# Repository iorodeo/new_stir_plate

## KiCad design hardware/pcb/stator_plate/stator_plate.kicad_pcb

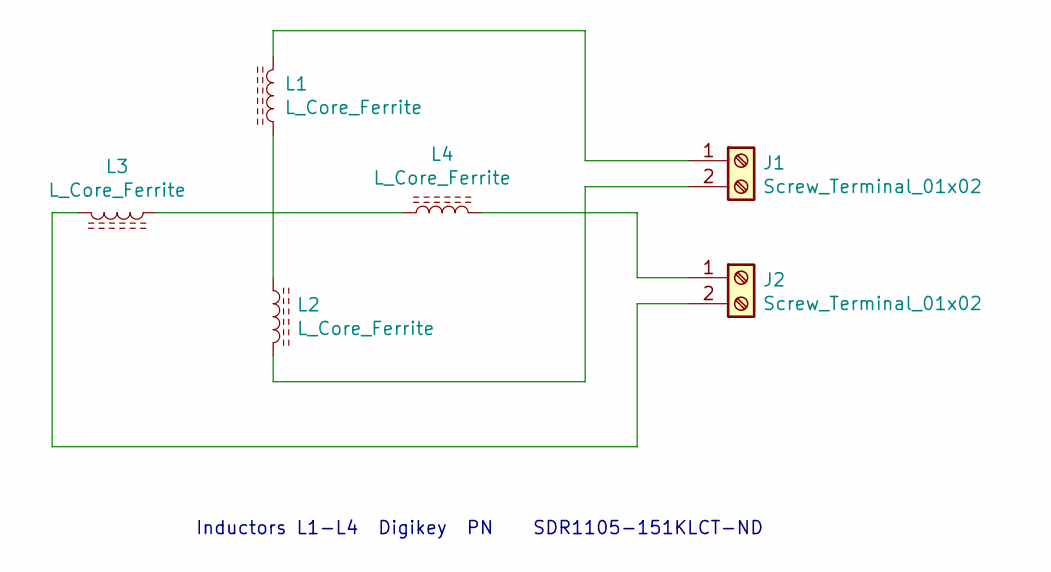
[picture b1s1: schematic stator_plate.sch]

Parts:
J1, J2: Screw_Terminal_01x02; CONNBLOCK2
L1, L2, L3, L4: L_Core_Ferrite; SDR1105

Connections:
unnamed: J1.1, L1.2
unnamed: J1.2, L2.2
unnamed: J2.1, L4.2
unnamed: J2.2, L3.2
unnamed: L1.1, L2.1
unnamed: L3.1, L4.1

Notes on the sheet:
Inductors L1-L4 Digikey PN SDR1105-151KLCT-ND

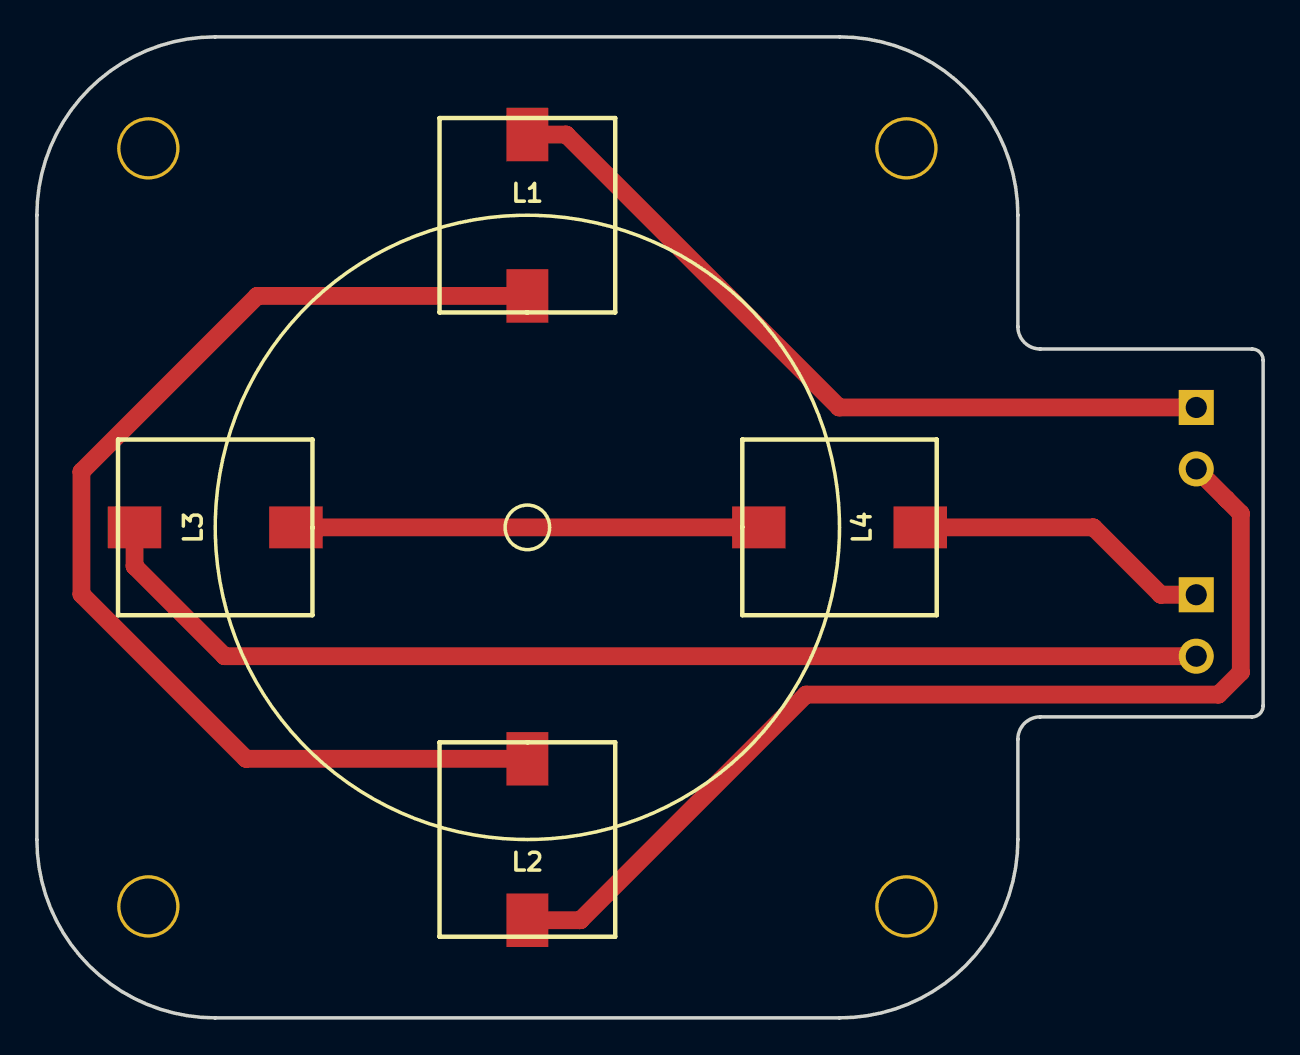
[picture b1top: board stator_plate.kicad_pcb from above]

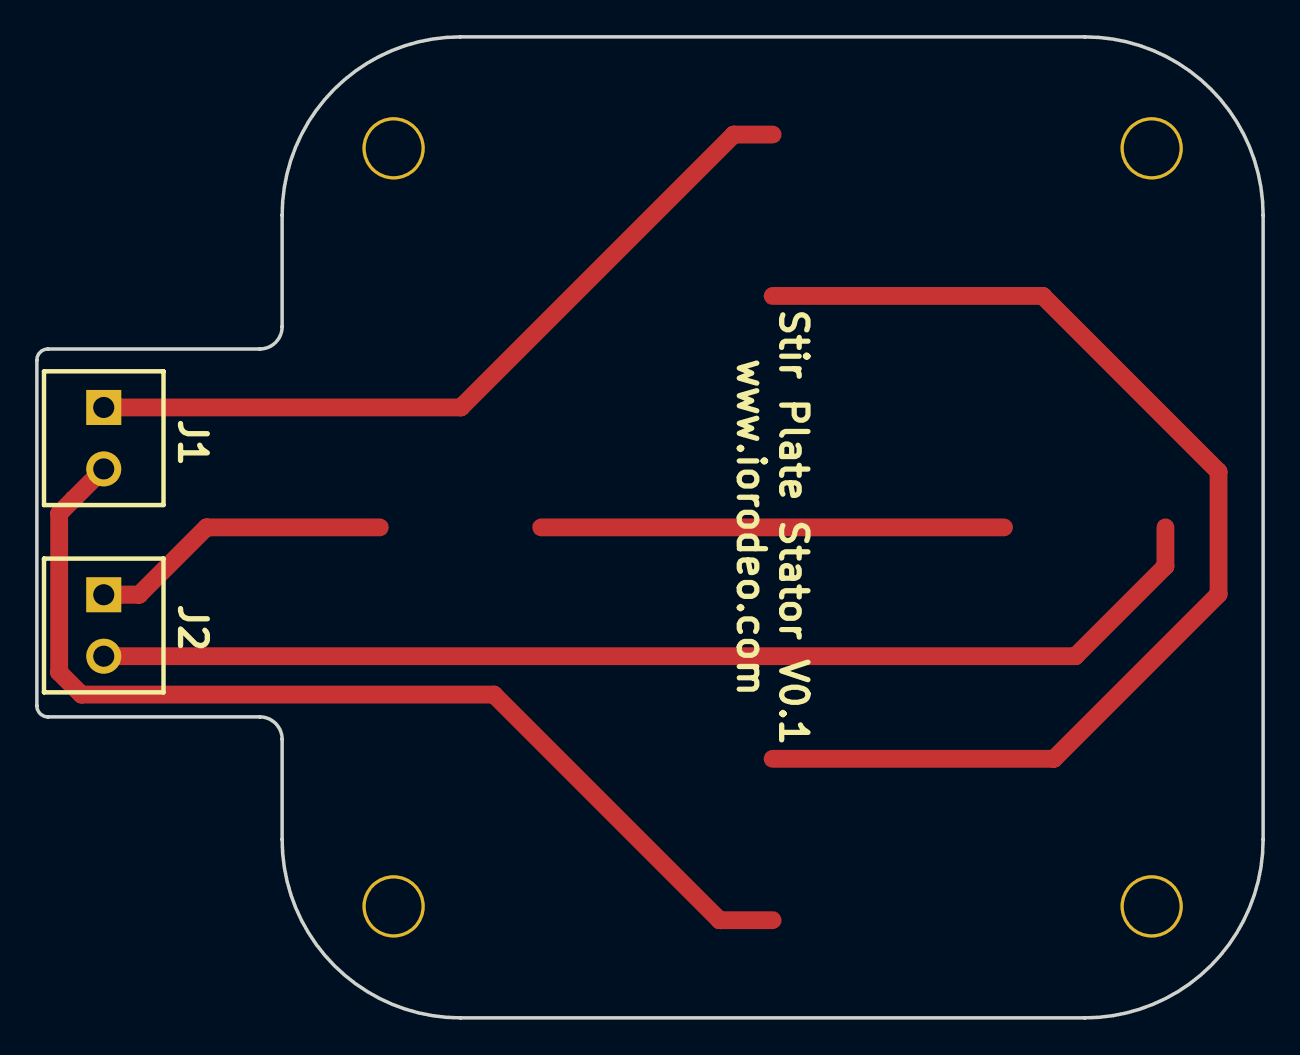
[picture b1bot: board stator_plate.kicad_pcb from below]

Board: 2 copper layers, 69.8 x 55.9 mm, 10 parts (2 on the bottom side), 6 nets.

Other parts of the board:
M1, M2, M3, M4: 4-40_mount_hole

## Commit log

2019-06-27 Finished initial design of stator plate.
